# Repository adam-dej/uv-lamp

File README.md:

uv-lamp
=======

Easy-to-construct UV lamp for exposition of PCB's with programmable timer, licensed under TAPR Open Hardware License.

This lamp is using 15 UV LEDs for PCB exposition. It can handle exposing 150x110 sized PCB's.

Schematic was created with KiCad.

Complete documentation and user manual is here: http://frozendevs.com/wiki/doku.php?id=wiki:uv-lamp

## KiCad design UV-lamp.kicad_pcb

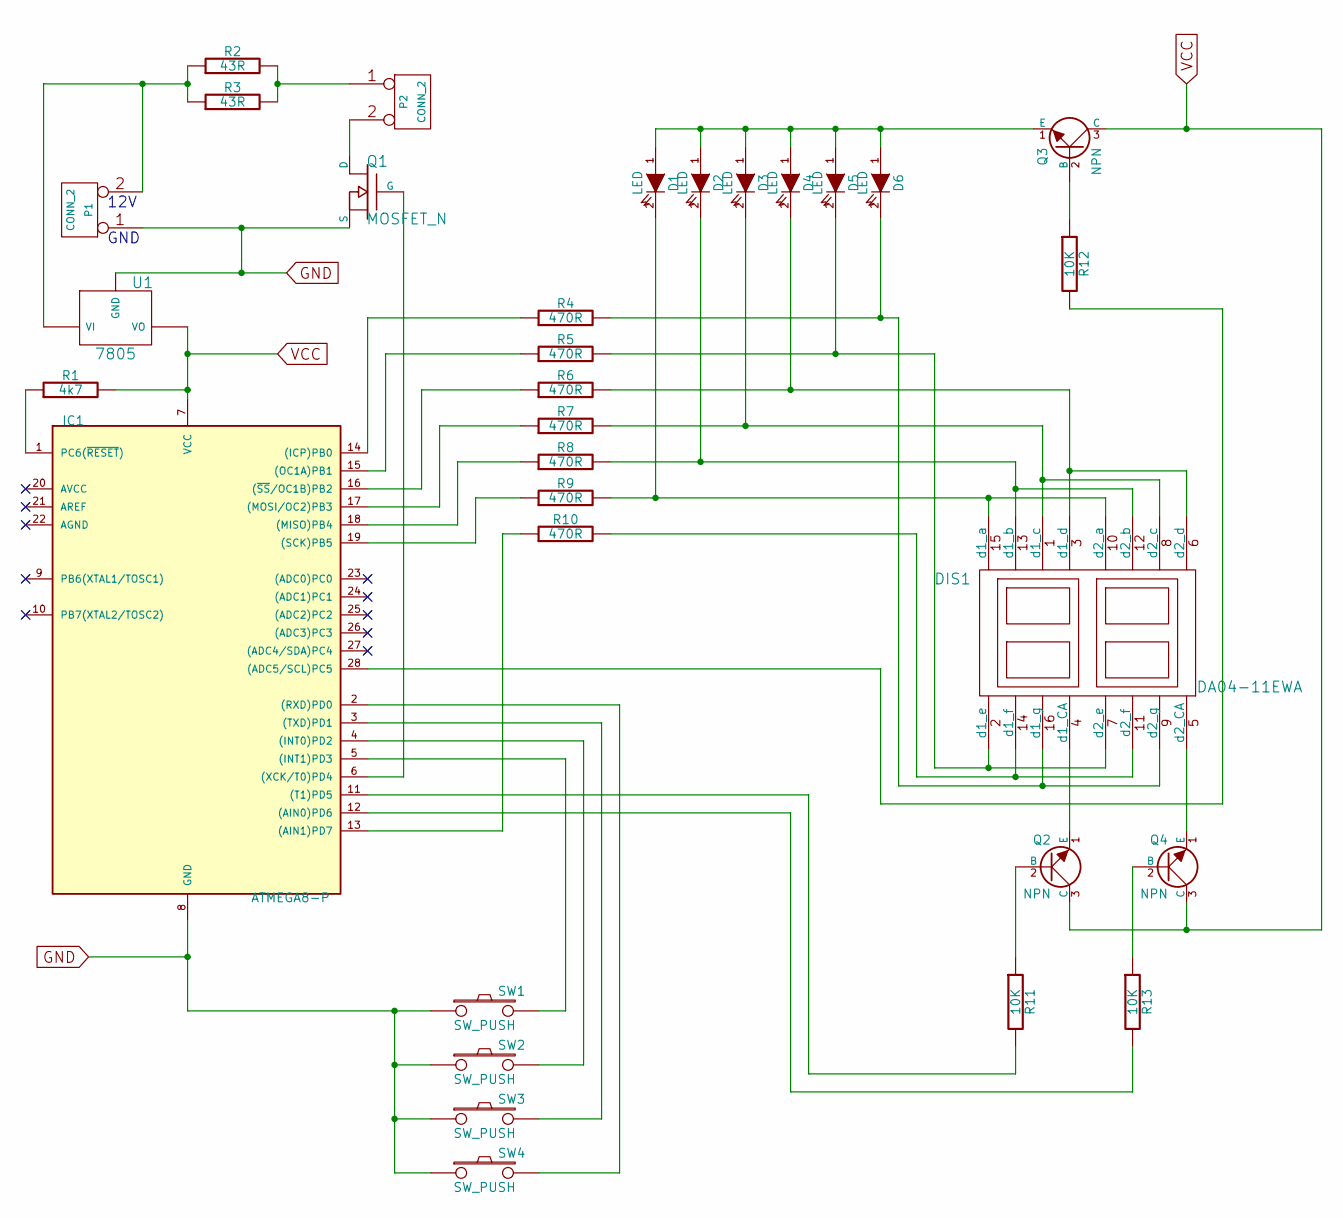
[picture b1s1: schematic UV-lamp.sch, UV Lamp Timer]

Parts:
D1, D2, D3, D4, D5, D6: LED
DIS1: DA04-11EWA
IC1: ATMEGA8-P; DIL28
P1, P2: CONN_2
Q1: MOSFET_N
Q2, Q3, Q4: NPN
R1: 4k7
R2, R3: 43R
R4, R5, R6, R7, R8, R9, R10: 470R
R11, R12, R13: 10K
SW1, SW2, SW3, SW4: SW_PUSH
U1: 7805

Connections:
GND: IC1.8 (GND), P1.1, Q1.S, SW1.1, SW2.1, SW3.1, SW4.1, U1.GND
unnamed: D1.1 (A), D2.1 (A), D3.1 (A), D4.1 (A), D5.1 (A), D6.1 (A), Q3.1 (E)
unnamed: IC1.28 ((ADC5/SCL)PC5), R12.2
unnamed: Q3.2 (B), R12.1
unnamed: IC1.19 ((SCK)PB5), R9.1
unnamed: IC1.13 ((AIN1)PD7), R10.1
unnamed: IC1.18 ((MISO)PB4), R8.1
unnamed: IC1.17 ((MOSI/OC2)PB3), R7.1
unnamed: IC1.5 ((INT1)PD3), SW1.2
unnamed: IC1.2 ((RXD)PD0), SW4.2
unnamed: P2.2 (PM), Q1.D
unnamed: IC1.3 ((TXD)PD1), SW3.2
unnamed: IC1.4 ((INT0)PD2), SW2.2
unnamed: DIS1.4 (d1_CA), Q2.1 (E)
unnamed: IC1.12 ((AIN0)PD6), R13.2
unnamed: DIS1.5 (d2_CA), Q4.1 (E)
unnamed: Q2.2 (B), R11.1
unnamed: Q4.2 (B), R13.1
unnamed: IC1.11 ((T1)PD5), R11.2
unnamed: D4.2 (K), DIS1.3 (d1_d), DIS1.6 (d2_d), R6.2
unnamed: IC1.1 (PC6(~RESET~)), R1.1
unnamed: P1.2 (PM), R2.1, R3.1, U1.VI
unnamed: D2.2 (K), DIS1.12 (d2_b), DIS1.13 (d1_b), R8.2
unnamed: IC1.15 ((OC1A)PB1), R5.1
unnamed: IC1.14 ((ICP)PB0), R4.1
unnamed: DIS1.11 (d2_f), DIS1.14 (d1_f), R10.2
unnamed: D1.2 (K), DIS1.10 (d2_a), DIS1.15 (d1_a), R9.2
unnamed: D6.2 (K), DIS1.9 (d2_g), DIS1.16 (d1_g), R4.2
unnamed: D3.2 (K), DIS1.1 (d1_c), DIS1.8 (d2_c), R7.2
unnamed: D5.2 (K), DIS1.2 (d1_e), DIS1.7 (d2_e), R5.2
unnamed: IC1.6 ((XCK/T0)PD4), Q1.G
unnamed: IC1.16 ((~SS~/OC1B)PB2), R6.1
unnamed: P2.1, R2.2, R3.2
VCC: IC1.7 (VCC), Q2.3 (C), Q3.3 (C), Q4.3 (C), R1.2, U1.VO

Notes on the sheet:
GND
12V

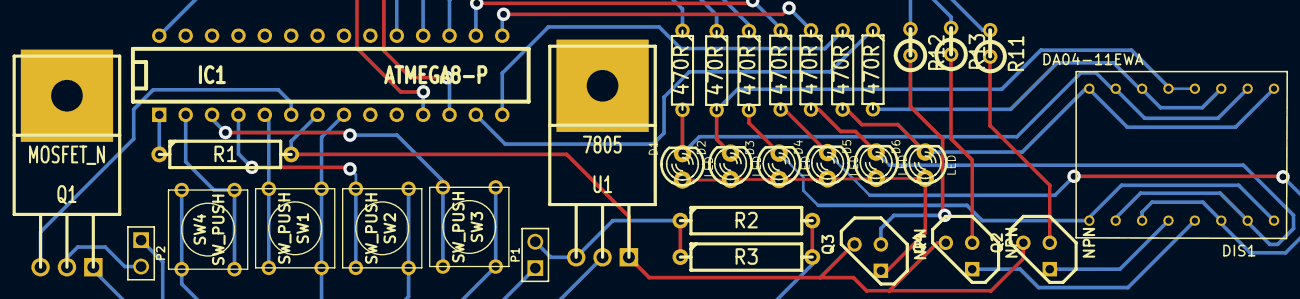
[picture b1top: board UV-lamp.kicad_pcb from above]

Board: 2 copper layers, 32 parts (0 on the bottom side), 34 nets.

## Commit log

2013-10-06 Commit revision B
2013-10-06 Add license notice to the schematic and PCB layout
2013-10-06 Add firmware source for AVR
